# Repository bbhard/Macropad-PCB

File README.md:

# Macropad-PCB

I have started designing and possiblytm manufacturing a macropad. This is a sideproject so don't expect much please.

## Iterations
Version | Description | Issues
--------|------------|-------
`V1` | This is the first iteration of the PCB designed to fit with a 3x4 macropad. |  Poor routing and not well thought out design. Lacking features. Not final, not functional.
`V1.1` | Improved on V1 by adding ESD chip and different shape. Overall more thought out design. | Not completly happy with the routing, much better than `V1`. WIP

## Disclaimer

* I don't really know what I'm doing, I started learning kicad this month
* This will never be sold *probably*

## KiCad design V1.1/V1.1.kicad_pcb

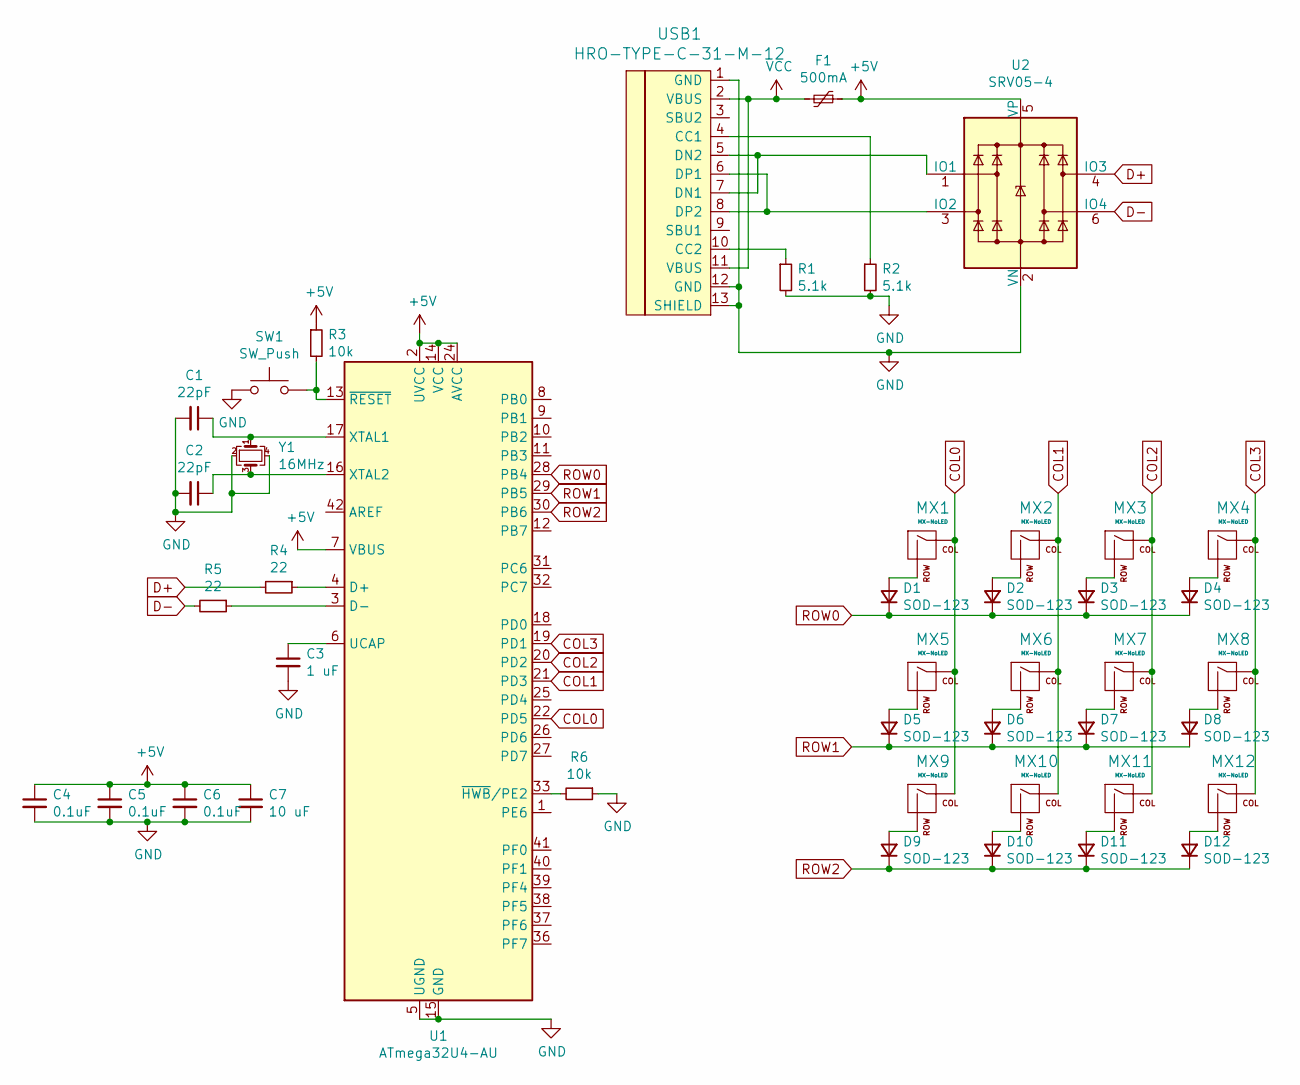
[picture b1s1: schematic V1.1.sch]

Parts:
C1, C2: 22pF; C_0805_2012Metric
C3: 1 uF; C_0805_2012Metric
C4, C5, C6: 0.1uF; C_0805_2012Metric
C7: 10 uF; C_0805_2012Metric
D1, D2, D3, D4, D5, D6, D7, D8, D9, D10, D11, D12: SOD-123; D_SOD-123
F1: 500mA; Fuse_1206_3216Metric
MX1, MX2, MX3, MX4, MX5, MX6, MX7, MX8, MX9, MX10, MX11, MX12: MX-NoLED; MXOnly-1U-NoLED
R1, R2: 5.1k; R_0805_2012Metric
R3, R6: 10k; R_0805_2012Metric
R4, R5: 22; R_0805_2012Metric
SW1: SW_Push; SKQG-1155865
U1: ATmega32U4-AU; TQFP-44_10x10mm_P0.8mm
U2: SRV05-4; SOT-23-6
USB1: HRO-TYPE-C-31-M-12; HRO-TYPE-C-31-M-12-Assembly
Y1: 16MHz; Crystal_SMD_3225-4Pin_3.2x2.5mm

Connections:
+5V: C4.1, C5.1, C6.1, C7.1, F1.1, R3.1, U1.2 (UVCC), U1.7 (VBUS), U1.14 (VCC), U1.24 (AVCC), U1.34 (VCC), U1.44 (AVCC), U2.5 (VP)
COL0: MX1.1 (COL), MX5.1 (COL), MX9.1 (COL), U1.22 (PD5)
COL1: MX2.1 (COL), MX6.1 (COL), MX10.1 (COL), U1.21 (PD3)
COL2: MX3.1 (COL), MX7.1 (COL), MX11.1 (COL), U1.20 (PD2)
COL3: MX4.1 (COL), MX8.1 (COL), MX12.1 (COL), U1.19 (PD1)
D+: R4.2, U2.4 (IO3)
D-: R5.2, U2.6 (IO4)
GND: C1.2, C2.2, C3.2, C4.2, C5.2, C6.2, C7.2, R1.2, R2.2, R6.1, SW1.1, U1.5 (UGND), U1.15 (GND), U1.23 (GND), U1.35 (GND), U1.43 (GND), U2.2 (VN), USB1.1 (GND), USB1.12 (GND), USB1.13 (SHIELD), Y1.2, Y1.4
unnamed: C1.1, U1.17 (XTAL1), Y1.1
unnamed: C2.1, U1.16 (XTAL2), Y1.3
unnamed: C3.1, U1.6 (UCAP)
unnamed: D1.2 (A), MX1.2 (ROW)
unnamed: D2.2 (A), MX2.2 (ROW)
unnamed: D3.2 (A), MX3.2 (ROW)
unnamed: D4.2 (A), MX4.2 (ROW)
unnamed: D5.2 (A), MX5.2 (ROW)
unnamed: D6.2 (A), MX6.2 (ROW)
unnamed: D7.2 (A), MX7.2 (ROW)
unnamed: D8.2 (A), MX8.2 (ROW)
unnamed: D9.2 (A), MX9.2 (ROW)
unnamed: D10.2 (A), MX10.2 (ROW)
unnamed: D11.2 (A), MX11.2 (ROW)
unnamed: D12.2 (A), MX12.2 (ROW)
unnamed: R1.1, USB1.10 (CC2)
unnamed: R2.1, USB1.4 (CC1)
unnamed: R3.2, SW1.2, U1.13 (~RESET)
unnamed: R4.1, U1.4 (D+)
unnamed: R5.1, U1.3 (D-)
unnamed: R6.2, U1.33 (~HWB~/PE2)
unnamed: U2.1 (IO1), USB1.5 (DN2), USB1.7 (DN1)
unnamed: U2.3 (IO2), USB1.6 (DP1), USB1.8 (DP2)
ROW0: D1.1 (K), D2.1 (K), D3.1 (K), D4.1 (K), U1.28 (PB4)
ROW1: D5.1 (K), D6.1 (K), D7.1 (K), D8.1 (K), U1.29 (PB5)
ROW2: D9.1 (K), D10.1 (K), D11.1 (K), D12.1 (K), U1.30 (PB6)
VCC: F1.2, USB1.2 (VBUS), USB1.11 (VBUS)

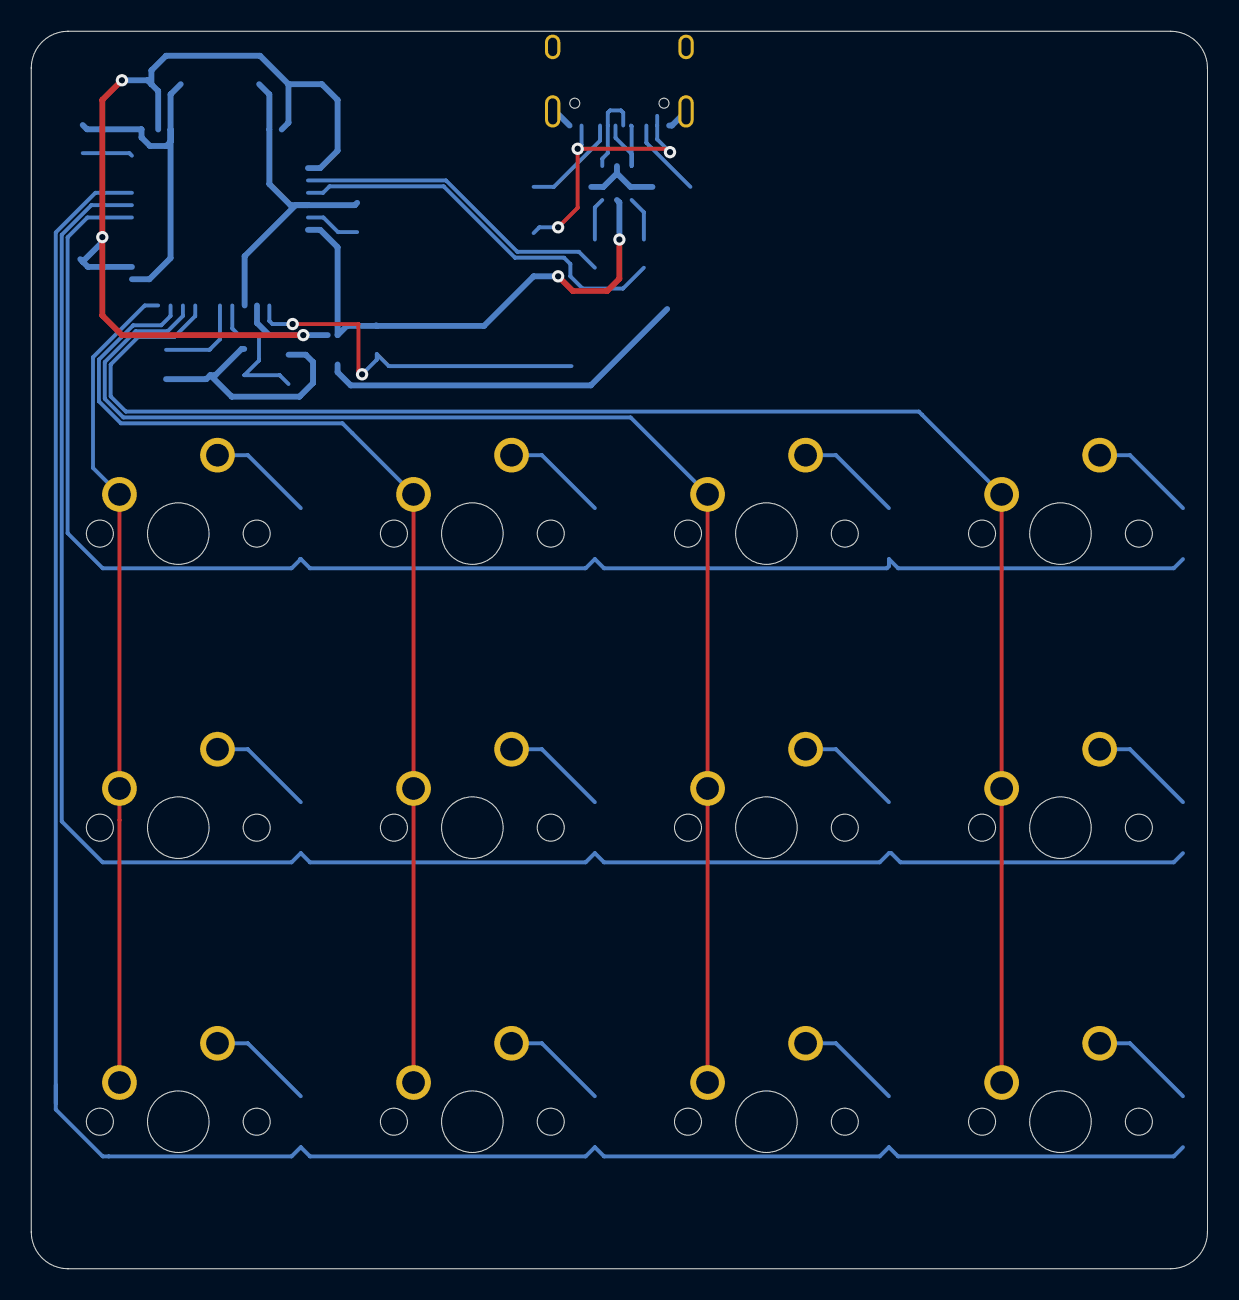
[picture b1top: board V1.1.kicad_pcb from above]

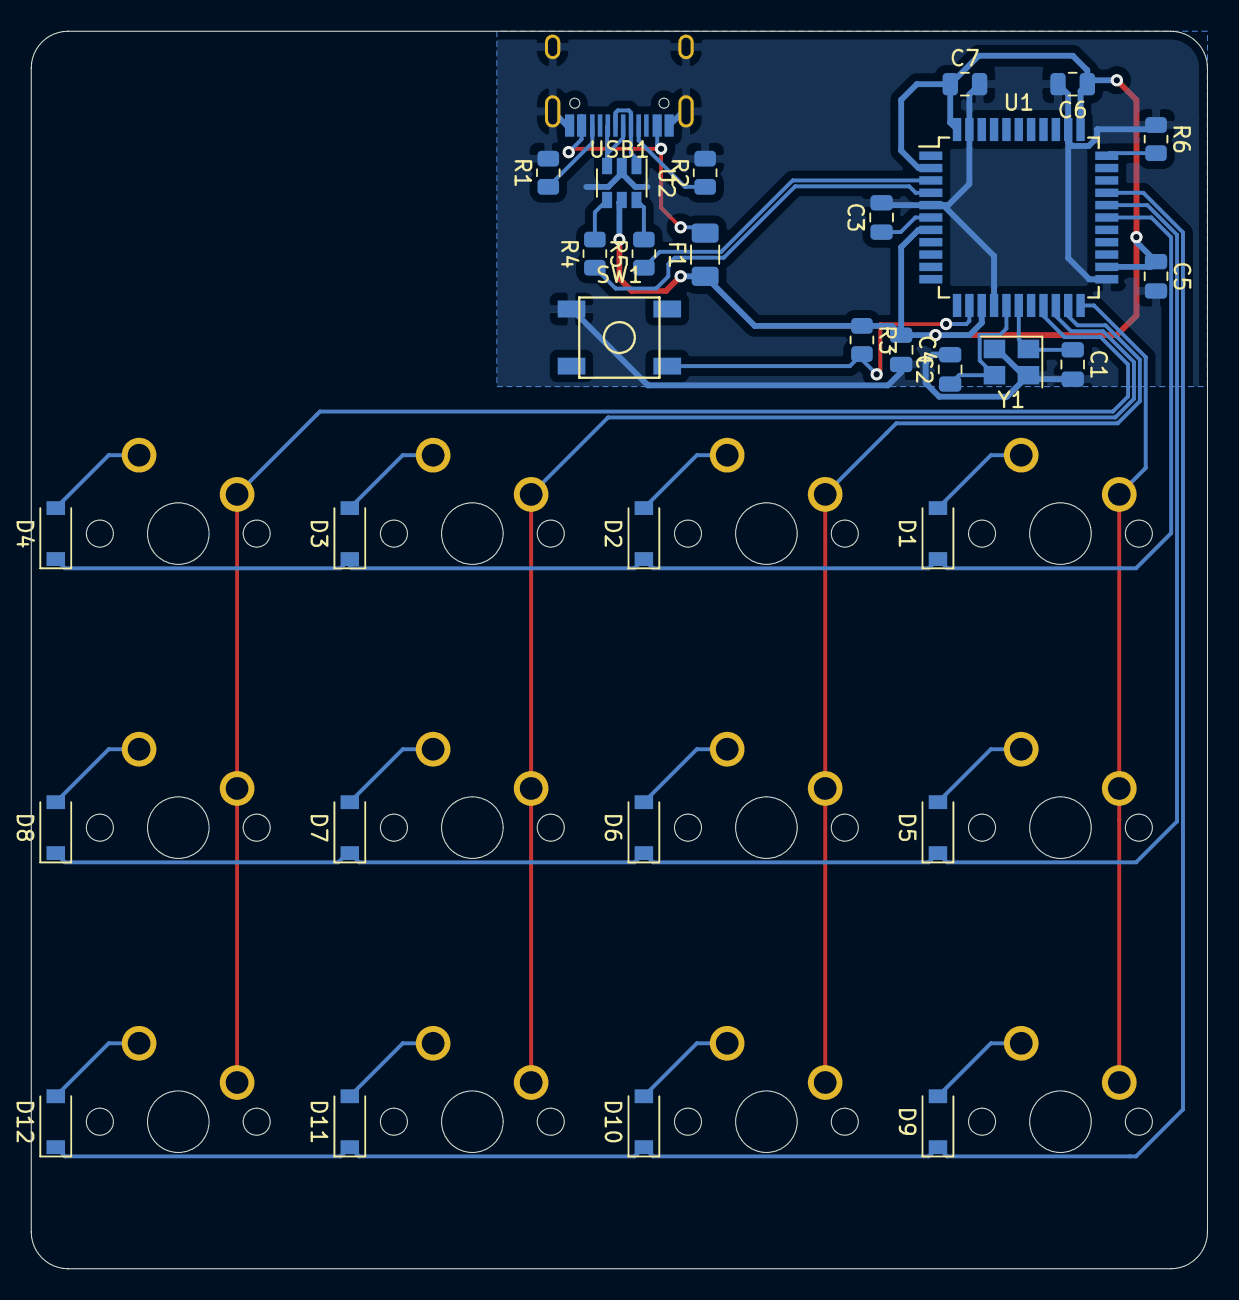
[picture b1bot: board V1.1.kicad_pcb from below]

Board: 2 copper layers, 76.2 x 80.2 mm, 43 parts (31 on the bottom side), 35 nets.

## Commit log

2021-10-31 About to create MCU
2021-10-31 Schematic done and Footprints assigned
2021-11-01 Fixed Type C wiring
2021-11-01 PCB and Routing done. Adjusted Type C connectors further
2021-11-01 Improved routing
2021-11-01 idek man
2021-11-02 Organized files
2021-11-02 Started V1.1. Considering to improve PCB design and added ESD chip.
2021-11-03 Footprints and minor changes
2021-11-03 deleted unnecessary files
2021-11-05 PCB and routing done
2021-11-05 Fixed routing errors
2021-11-06 Fixed routing even further
2021-11-13 Added images, organized files
2021-11-14 Updated traces to not be as close to decoupling capacitor
